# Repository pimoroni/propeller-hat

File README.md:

Propeller HAT, the 8-core microcontroller add-on for your Raspberry Pi.

Available now from Pimoroni: http://shop.pimoroni.com/products/propeller-hat

Propeller HAT is licensed under a Creative Commons Attribution-ShareAlike 4.0 International License.: http://creativecommons.org/licenses/by-sa/4.0/

### Features

* 8-core Parallax Microcontroller on-board
* 30 IO pins broken out, serial data/programming connection to Pi
* 20 Pi pins broken out for communications/ease of access
* 170pt breadboard for experimentation
* Python quick start library with PWM/Servo and GPIO libraries

### Getting started

For instant-gratification you can try the Propeller HAT IO libraries:

* [IO using Serial](documentation/Serial-IO.md)
* [IO using i2c](documentation/IO.md)
* [PWM for LEDs/Servos](documentation/PWM.md)

You'll need Propeller IDE to start programming your Propeller HAT:

* [Propeller IDE Getting Started](/documentation/Propeller-IDE-Getting-Started.md)

## Propeller IDE Installation

As always, we've made it super-easy for you to get all the software you need with a nifty one-line installer. To run it fire up Terminal which you'll find in Menu -> Accessories -> Terminal on your Raspberry Pi desktop like so:

In the new terminal window type:

```bash
curl -sS get.pimoroni.com/propellerhat | bash
```

This will install a fairly recent version of the Propeller IDE but if you'd like you can head over to [www.lamestation.com/propelleride/](http://www.lamestation.com/propelleride/) and grab the latest
version of Propeller IDE for the Raspberry Pi, which may be newer than the one installed by the one-line installer.

It's easier if you grab the right URL, and use the wget command on your
Raspberry Pi to download it. For example:

```bash
wget https://github.com/parallaxinc/PropellerIDE/releases/download/0.36.7/propelleride-0.36.7-armhf.deb
```

Once downloaded, you can install it with:

```bash
sudo dpkg -i propelleride-0.36.7-armhf.deb
```

### Documentaton & Support

* Tutorials - https://learn.pimoroni.com/propeller-hat
* GPIO Pinout - https://pinout.xyz/pinout/propeller_hat
* Get help - http://forums.pimoroni.com/c/support

### Repository Contents

#### Documentation

Everything you need to get started with Propeller IDE and your first
SPIN program.

#### Software

Suport software and Python-based uploader tool.

* python - Python library for Propeller HAT with PWM and GPIO functions
* sidplay - Play SID tune dumps with Propeller HAT
* p1load - Installer and binary for Pi-compatible p1load

#### Datasheets

Datasheets for Parallax Propeller and Crystal Oscillator.

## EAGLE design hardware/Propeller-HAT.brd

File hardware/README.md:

# Propeller HAT Hardware

## License

Propeller HAT is licensed under a Creative Commons Attribution-ShareAlike 4.0 International License.: http://creativecommons.org/licenses/by-sa/4.0/

#### This license covers:

* Propeller HAT board design and schematic layout - Propeller-HAT.brd, Propeller-HAT.sch

#### This license does *not* cover:

* The Parallax Propeller chip itself<sup>1</sup>
* Supporting ICs and components used on the Propeller HAT
* Logos or silkscreen artwork

<sup>1</sup> The Parallax Propeller is licensed under the GNU GPL 3.0, you can find the HDL source to the microcontroller, plus more information, here: http://www.parallax.com/microcontrollers/propeller-1-open-source

#### This license allows you to:

* Share — copy and redistribute the material in any medium or format
* Adapt — remix, transform, and build upon the material for any purpose, even commercially.

#### However, you must:

* give appropriate credit, provide a link to the license, and indicate if changes were made. You may do so in any reasonable manner, but not in any way that suggests we endorse you or your use.
* distribute your contributions under the same license as the original if you remix, transform, or build upon this material.

## Pinout

All Propeller IO is broken out in the horizontal pin headers. Note: The TX/RX pins, while available to the IC as general purpose IO pins normally, are tied to the GPIO of the Raspberry Pi and thus cannot be used.

Pins A29 and A28 are EEPROM SDA and SCL respectively. A 24LC512-I/P<sup>1</sup> EEPROM is recommended, and will require 10K pullup resistors. Once added, the Propeller will allow uploads to EEPROM and will load its contents upon boot.

## Bill Of Materials

* 1 x P8X32A-Q44 - QFP Parallax Propeller IC
* 1 x ABLS3-6.000MHZ-D4Y-T - 6Mhz Crystal Oscillator
* 1 x AP7333-__SRG - 300mA, 3.3V Voltage Regulator
* 1 x EEPROM - for Raspberry HAT compatibility
* 1 x 40PIN Low Profile Female SMD Header
* 1 x 10K Resistor R0603
* 2 x 4.7K Resistor R0603
* 1 x 1K Resistor R0603
* 4 x 0.1uF Capacitor C0603K
* 2 x 1uF Capacitor C0603K

## Crystal

6Mhz was chosen for a conservative overclock, but should be well within the range of values a P8X32A chip can tolerate under normal hobbyist operating conditions. PropellerHAT can operate on a 4Mhz-8Mhz variant of the ABLS3 Crystal. Typical clock speeds at a PLL of 16 to 2x include:

| Xin  | 16x     | 8x    | 4x    | 2x    |
|------|---------|-------|-------|-------|
| 8Mhz | 128Mhz* | 64Mhz | 32Mhz | 16Mhz |
| 6Mhz | 96Mhz   | 48Mhz | 24Mhz | 12Mhz |
| 5Mhz | 80Mhz   | 40Mhz | 20Mhz | 10Mhz |

*Speed not supported or recommended.

* [ABLS3 Crystal Oscillator datasheet](/datasheets/Crystal-OSC-ABLS3-25529.pdf)

* <sup>1</sup> http://uk.mouser.com/ProductDetail/Microchip-Technology/24LC512-I-P/?qs=JmwSjbzn2OL8zYUOM6epRw%3D%3D

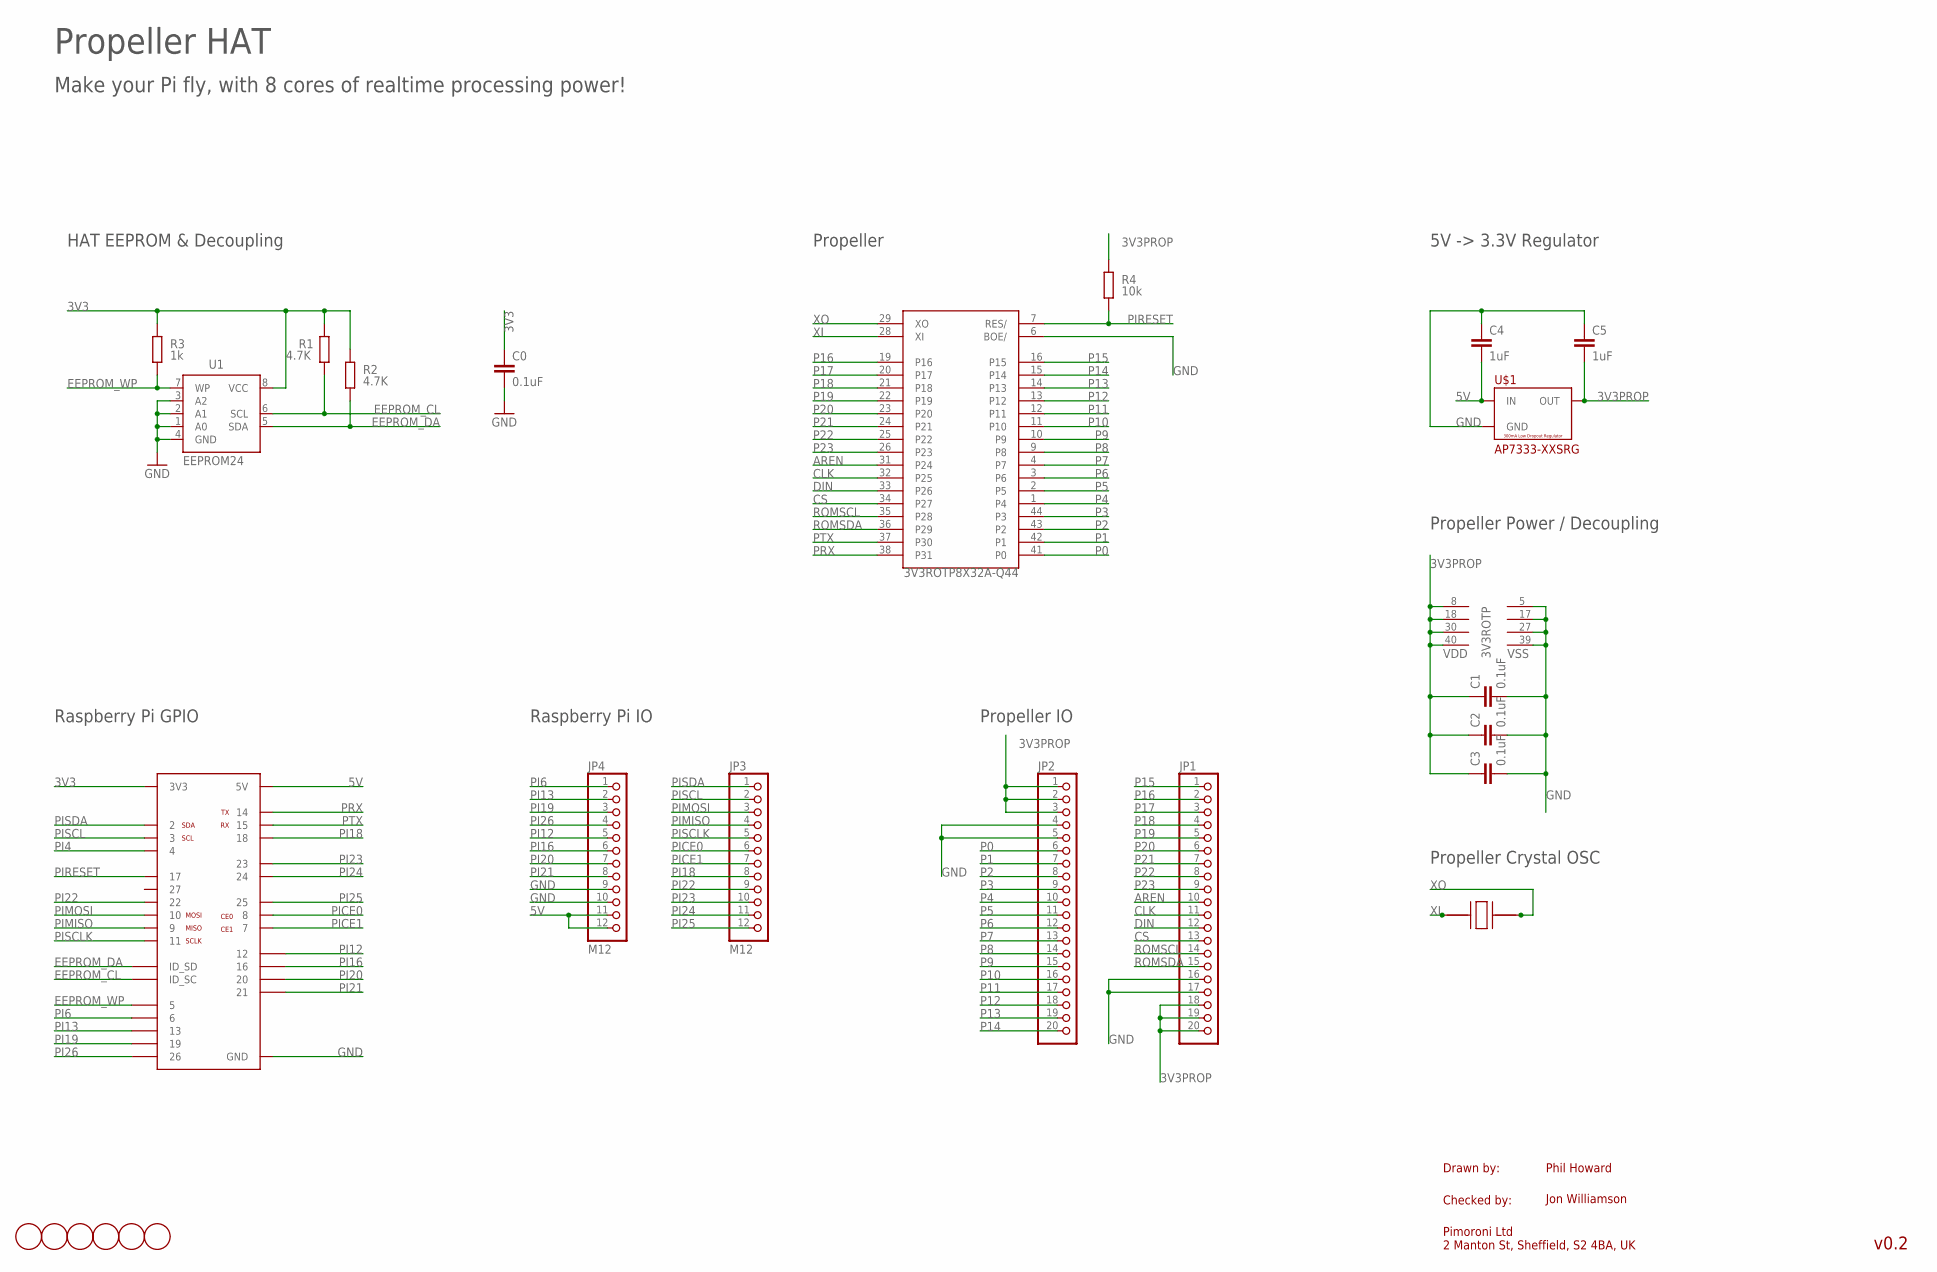
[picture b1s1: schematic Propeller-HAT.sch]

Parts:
3V3ROT: P8X32A-Q44
C0, C1, C2, C3: 0.1uF; C0603K
C4, C5: 1uF; C0603K
JP1, JP2: PINHD-1X20-BIG; 1X20-BIG
JP3, JP4: M12
R1, R2: 4.7K; R0603; TOLERANCE 5%
R3: 1k; R0603; TOLERANCE 5%
R4: 10k; R0603; TOLERANCE 5%
U1: EEPROM24; SOIC8
U$1: AP7333-XXSRG; SOT23
U$2: RPIGPIOPINHD-2X20-SMD-FLIPPED; FCI_89898_313LF_40P_CONNECTOR_SMT_FLIPPED
U$3, U$4, U$5, U$6, U$7, U$8: FIDUCIAL1MM; FIDUCIAL-1MM
U$9: ABLS3-XXXMHZ-D4Y-T

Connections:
3V3: C0.1, R1.2, R2.2, R3.2, U1.8 (VCC), U$2.P1_3V3 (3V3), U$2.P17_3V3 (3V3)
3V3PROP: 3V3ROT.8 (VDD), 3V3ROT.18 (VDD), 3V3ROT.30 (VDD), 3V3ROT.40 (VDD), C1.1, C2.1, C3.1, C5.2, JP1.18, JP1.19, JP1.20, JP2.1, JP2.2, JP2.3, R4.2, U$1.2 (OUT)
5V: C4.2, JP4.11, JP4.12, U$1.3 (IN), U$2.P2_5V (5V), U$2.P4_5V (5V)
AREN: 3V3ROT.31 (P24), JP1.10
CLK: 3V3ROT.32 (P25), JP1.11
CS: 3V3ROT.34 (P27), JP1.13
DIN: 3V3ROT.33 (P26), JP1.12
EEPROM_CL: R1.1, U1.6 (SCL), U$2.P28_IDSC (ID_SC)
EEPROM_DA: R2.1, U1.5 (SDA), U$2.P27_IDSD (ID_SD)
EEPROM_WP: R3.1, U1.7 (WP), U$2.P29_GPIO5 (5)
GND: 3V3ROT.5 (VSS), 3V3ROT.6 (BOE/), 3V3ROT.17 (VSS), 3V3ROT.27 (VSS), 3V3ROT.39 (VSS), C0.2, C1.2, C2.2, C3.2, C4.1, C5.1, JP1.16, JP1.17, JP2.4, JP2.5, JP4.9, JP4.10, U1.1 (A0), U1.2 (A1), U1.3 (A2), U1.4 (GND), U$1.1 (GND), U$2.P6_GND (GND), U$2.P9_GND (GND), U$2.P14_GND (GND), U$2.P20_GND (GND), U$2.P25_GND (GND), U$2.P30_GND (GND), U$2.P34_GND (GND), U$2.P39_GND (GND)
P0: 3V3ROT.41 (P0), JP2.6
P1: 3V3ROT.42 (P1), JP2.7
P2: 3V3ROT.43 (P2), JP2.8
P3: 3V3ROT.44 (P3), JP2.9
P4: 3V3ROT.1 (P4), JP2.10
P5: 3V3ROT.2 (P5), JP2.11
P6: 3V3ROT.3 (P6), JP2.12
P7: 3V3ROT.4 (P7), JP2.13
P8: 3V3ROT.9 (P8), JP2.14
P9: 3V3ROT.10 (P9), JP2.15
P10: 3V3ROT.11 (P10), JP2.16
P11: 3V3ROT.12 (P11), JP2.17
P12: 3V3ROT.13 (P12), JP2.18
P13: 3V3ROT.14 (P13), JP2.19
P14: 3V3ROT.15 (P14), JP2.20
P15: 3V3ROT.16 (P15), JP1.1
P16: 3V3ROT.19 (P16), JP1.2
P17: 3V3ROT.20 (P17), JP1.3
P18: 3V3ROT.21 (P18), JP1.4
P19: 3V3ROT.22 (P19), JP1.5
P20: 3V3ROT.23 (P20), JP1.6
P21: 3V3ROT.24 (P21), JP1.7
P22: 3V3ROT.25 (P22), JP1.8
P23: 3V3ROT.26 (P23), JP1.9
PI4: U$2.P7_GPIO4 (4)
PI6: JP4.1, U$2.P31_GPIO6 (6)
PI12: JP4.5, U$2.P32_GPIO12 (12)
PI13: JP4.2, U$2.P33_GPIO13 (13)
PI16: JP4.6, U$2.P36_GPIO16 (16)
PI18: JP3.8, U$2.P12_GPIO18 (18)
PI19: JP4.3, U$2.P35_GPIO19 (19)
PI20: JP4.7, U$2.P38_GPIO20 (20)
PI21: JP4.8, U$2.P40_GPIO21 (21)
PI22: JP3.9, U$2.P15_GPIO22 (22)
PI23: JP3.10, U$2.P16_GPIO23 (23)
PI24: JP3.11, U$2.P18_GPIO24 (24)
PI25: JP3.12, U$2.P22_GPIO25 (25)
PI26: JP4.4, U$2.P37_GPIO26 (26)
PICE0: JP3.6, U$2.P24_GPIO8_SPI0_CE0 (8)
PICE1: JP3.7, U$2.P26_GPIO7_SPI0_CE1 (7)
PIMISO: JP3.4, U$2.P21_GPIO9_SPI0_MISO (9)
PIMOSI: JP3.3, U$2.P19_GPIO10_SPI0_MOSI (10)
PIRESET: 3V3ROT.7 (RES/), R4.1, U$2.P11_GPIO17 (17)
PISCL: JP3.2, U$2.P5_GPIO3_SCL (3)
PISCLK: JP3.5, U$2.P23_GPIO11_SPI0_SCLK (11)
PISDA: JP3.1, U$2.P3_GPIO2_SDA (2)
PRX: 3V3ROT.38 (P31), U$2.P8_GPIO14_UART0_TXD (14)
PTX: 3V3ROT.37 (P30), U$2.P10_GPIO15_UART0_RXD (15)
ROMSCL: 3V3ROT.35 (P28), JP1.14
ROMSDA: 3V3ROT.36 (P29), JP1.15
XI: 3V3ROT.28 (XI), U$9.P$1 (1)
XO: 3V3ROT.29 (XO), U$9.P$2 (3)

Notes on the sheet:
Drawn by:
Checked by:
Pimoroni Ltd 2 Manton St, Sheffield, S2 4BA, UK
Phil Howard
v0.2
Propeller HAT
HAT EEPROM & Decoupling
Raspberry Pi GPIO
Make your Pi fly, with 8 cores of realtime processing power!
Jon Williamson
Propeller Power / Decoupling
Propeller Crystal OSC
5V -> 3.3V Regulator
Propeller IO
Raspberry Pi IO
Propeller

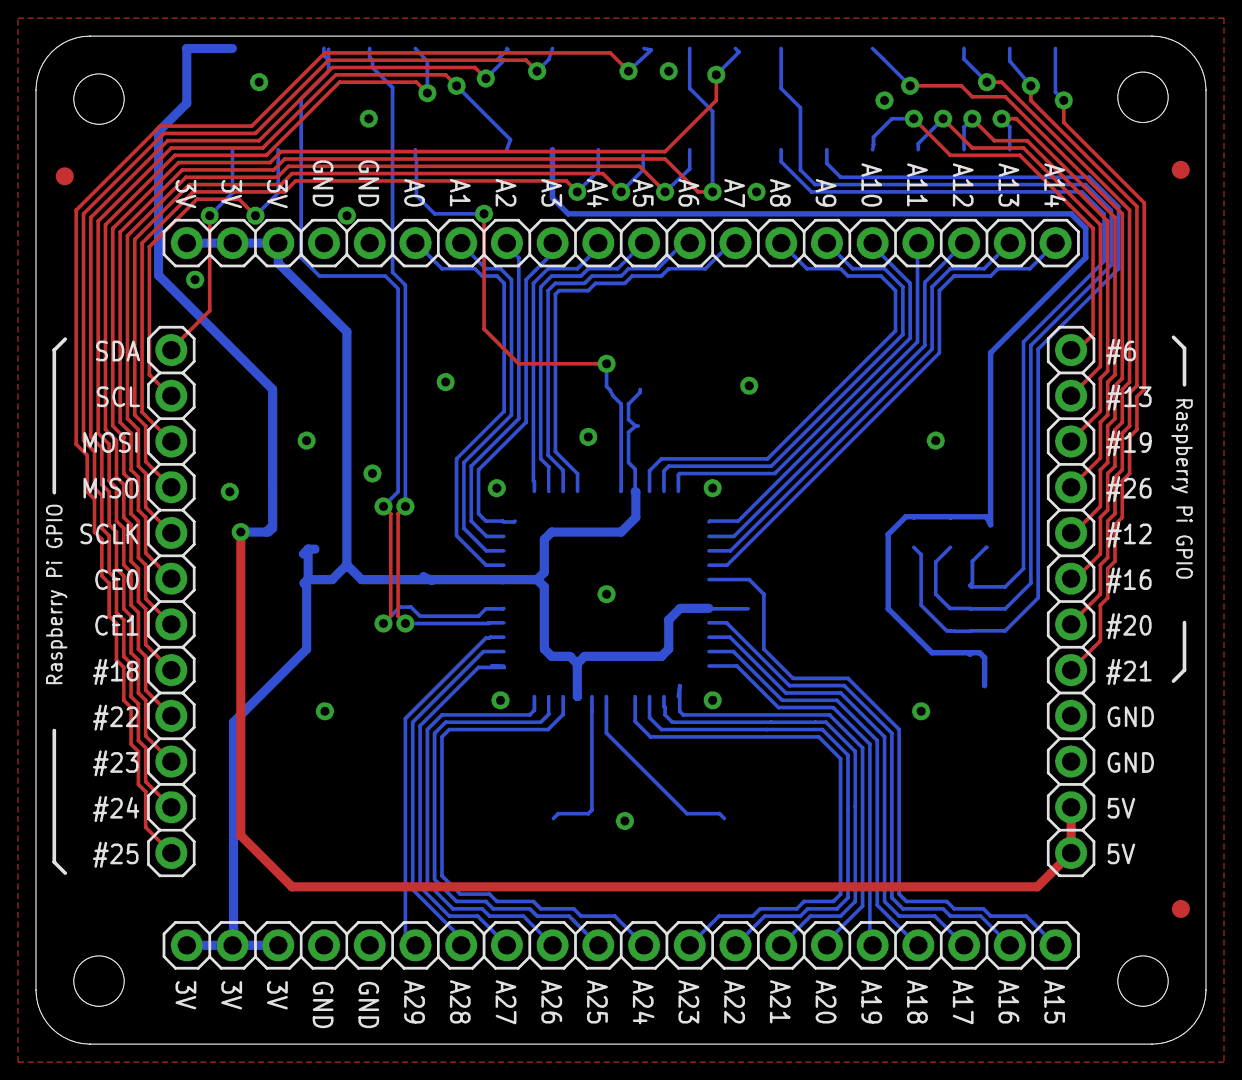
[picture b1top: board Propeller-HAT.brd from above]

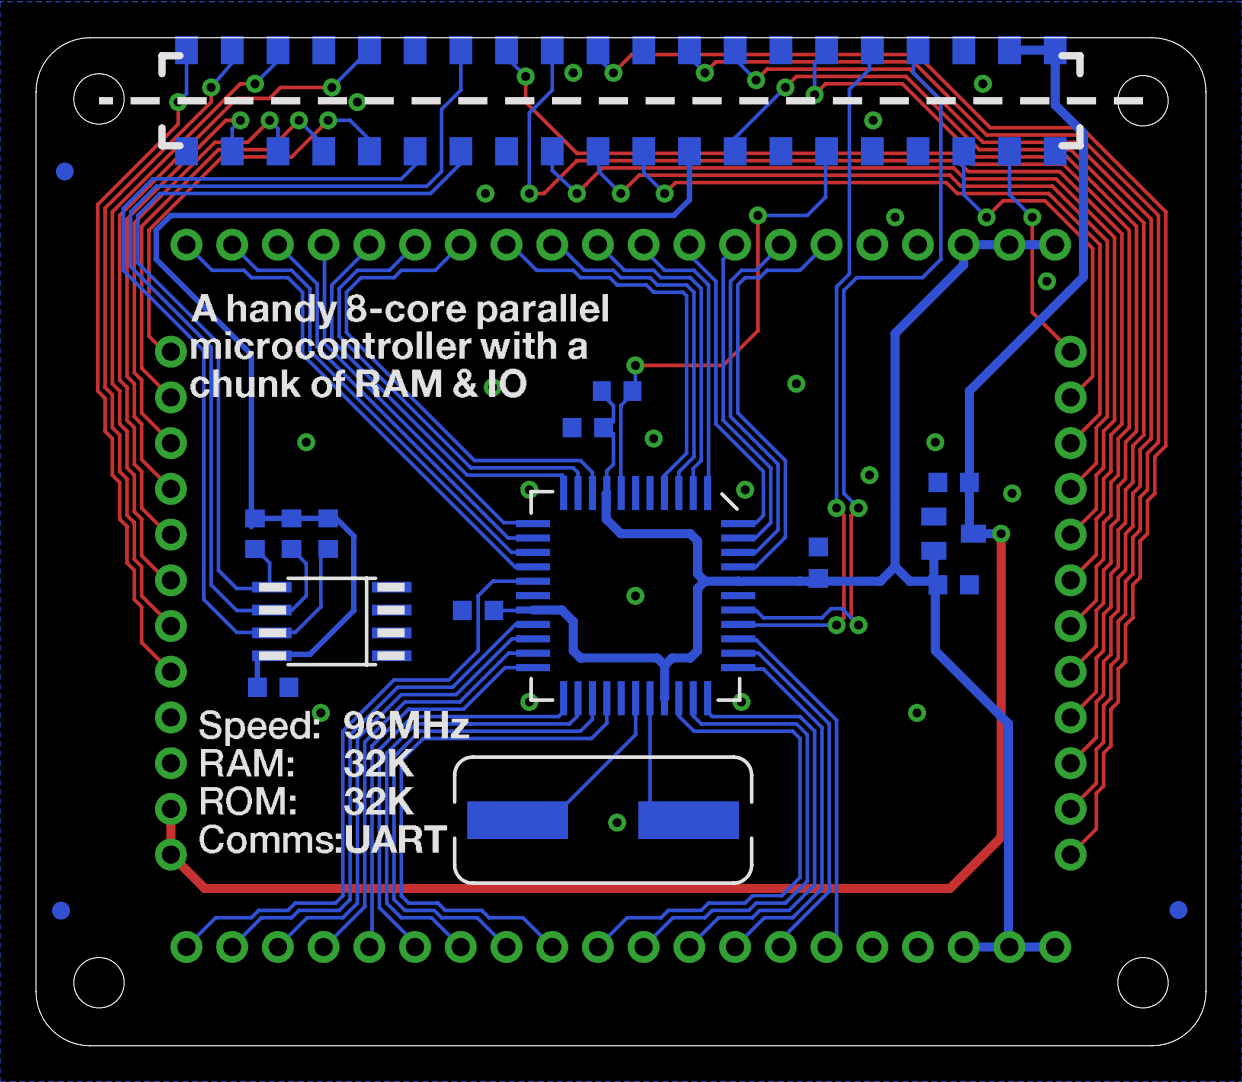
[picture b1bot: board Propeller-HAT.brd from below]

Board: 2 copper layers, 65.0 x 56.0 mm, 25 parts (18 on the bottom side), 62 nets.

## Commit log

2015-02-09 Added serial terminal image
2015-02-16 Updated sidplay with graceful exit
2015-02-23 Tidied up SIDcog serial player and source
2015-02-23 Added p1load binary, updated documentation
2015-02-23 Added logo
2015-02-25 Rainbow SPIN image
2015-02-25 Added example code
2015-02-26 New playlist
2015-03-01 Hub Cog Diagram
2015-03-02 Initial commit of tidied schematic and board files for Cadsoft Eagle
2015-03-02 Added multicore example code
2015-03-02 Added multicore layout graphic
2015-03-02 Fixed typos in example code
2015-03-02 Basic COG signalling example
2015-03-04 Update with dependency install for libftdi1
    Thanks Sandy! Fix for https://github.com/pimoroni/propeller-hat/issues/1
2015-03-04 First spin layout
2015-03-04 Update Your-first-SPIN-program.md
    Fixed silly, silly mistake!
2015-03-05 Added PASM example and new readme
2015-03-05 New example code for passing params in PASM
2015-03-05 Start of Passing params doc
2015-03-05 Fixed pin numbers in exmaples from bytes to longs, they're masks doh
2015-03-05 Corrected shift comment
2015-03-06 Added eeprom layout
2015-03-13 Added PDF schematic
2015-03-13 Corrected EEPROM part number to I2C version
2015-03-13 Propeller HAT Fritzing part and SVG
2015-03-27 Update README.md
    Added store link!
2015-04-02 Fixed a small typo ;)
2015-04-20 Replaced FullDuplexSerial with fixed encoding
2015-04-24 Updated to 0.30.1 install instructions
2015-04-30 Added learning portal markup
2015-05-03 Update Serial-IO.md
    not sure what is intended but I guess it should either be '30 and 31' or '31 and 32'... the former seems strictly logical given the example and the context of the word 'pin'?
2015-05-03 Update Propeller-IDE-Getting-Started.md
    I'm not a fan of adding repository to sources.list and leaving them active once they have served their purpose. In this case, at thispoint in time they would enforce upgardes of the follwoing on my s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
    libraspberrypi-bin libraspberrypi-dev libraspberrypi-doc libraspberrypi0 raspberrypi-bootloader
    maybe I'm funny and all that but I'm not keen on it ;-)
2016-01-11 Updated documentation to reflect new release
2016-01-11 Changed instructions to 0.33.3 for working propman
2016-01-11 Added note about 0.34.4 loader woes
2016-03-18 New instructions for Pi 3, now recommending 0.36.7
2016-03-22 Removed pins, inlined AsyncWorker
2016-08-23 p1load readme updated
2016-08-23 main README revised
2016-08-23 tidy up of release files
2016-08-23 src spin code moved to new examples directory
2016-08-23 setup.py standardised to other repo
2016-08-23 gitignore .binary files
2016-08-24 added makefile for io-pwm
2016-08-24 dependency for pyserial added
2016-08-24 try clause for pyserial and smbus
2016-08-24 p1load README reworded
2016-08-24 debian packaging
2016-08-24 sidplay import with try clauses
2016-08-24 README tweak
2016-08-24 moved doc examples with the rest
2016-08-24 io-serial rename to serialio
2016-08-24 src back in place
2016-09-06 .DS_Store added to .gitignore
2016-11-08 sys.exit used where appropriate + change to debian control files
2016-11-09 bug fix for setup.py version touch up
2016-11-09 closing ' for safety
2017-04-28 Added MIT license file to root
2017-04-28 Updated MIT license file to Pimoroni Ltd.
2017-05-03 Fixed headers

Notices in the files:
README.md:
CC BY-SA 4.0
parts and their libraries:
pimoroni: Licensing: CC v3.0 Share-Alike You are welcome to use this library for commercial purposes.
SparkFun-DigitalIC: Licensing: Creative Commons ShareAlike 4.0 International - https://creativecommons.org/licenses/by-sa/4.0
